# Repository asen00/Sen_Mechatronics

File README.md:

# MECH_ENG 433: Advanced Mechatronics
Northwestern University [MECH_ENG 433: Advanced Mechatronics](https://www.mccormick.northwestern.edu/mechanical/academics/courses/descriptions/433-advanced-mechatronics.html) taught by Nick Marchuk, Spring 2023

Details about assignments can be found [here](https://github.com/ndm736/ME433_2023/wiki).

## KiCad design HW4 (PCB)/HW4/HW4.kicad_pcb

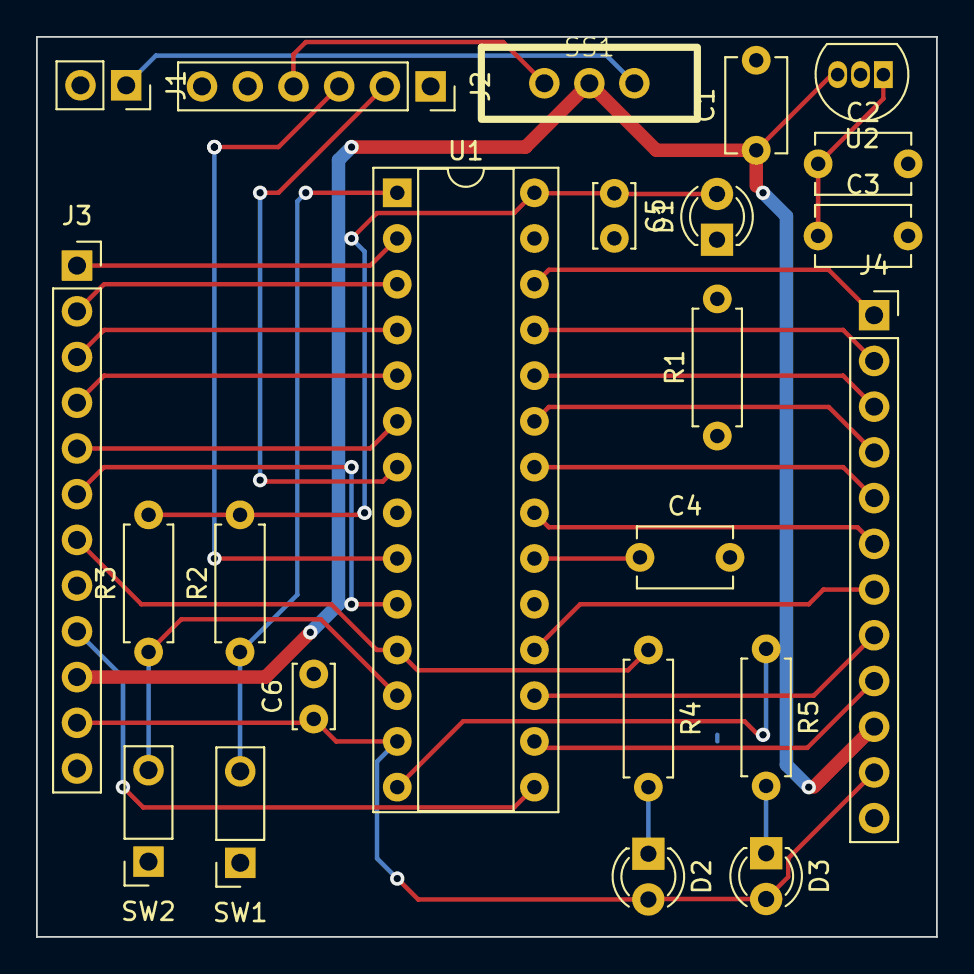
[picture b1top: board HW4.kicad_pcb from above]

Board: 2 copper layers, 50.0 x 50.0 mm, 23 parts (0 on the bottom side), 29 nets.

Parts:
C1, C2, C3, C4: 1 uF; C_Disc_D5.1mm_W3.2mm_P5.00mm
C5, C6: 0.1 uF; C_Disc_D3.4mm_W2.1mm_P2.50mm
D1: RED; LED_D3.0mm
D2: GREEN; LED_D3.0mm
D3: YELLOW; LED_D3.0mm
J1: BATTERY; PinSocket_1x02_P2.54mm_Vertical
J2: CP2102; PinSocket_1x06_P2.54mm_Vertical
J3: LEFT; PinSocket_1x12_P2.54mm_Vertical
J4: RIGHT; PinSocket_1x12_P2.54mm_Vertical
R1, R4, R5: 330; R_Axial_DIN0207_L6.3mm_D2.5mm_P7.62mm_Horizontal
R2, R3: 10k; R_Axial_DIN0207_L6.3mm_D2.5mm_P7.62mm_Horizontal
SS1: SLIDE; SlideSwitch
SW1: MCLR; PushButton
SW2: USER; PushButton
U1: PIC32; DIP-28_W7.62mm_Socket
U2: AP7381-33V; TO-92L_Inline

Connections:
+3.3V: C2.1, C3.1, C6.1, D2.2 (A), D3.2 (A), J3.11, J4.11, U1.13 (VDD), U2.1 (VO)
+5V: J2.4, SS1.1
/A0: J3.1, U1.2 (A0)
/A1: J3.2, U1.3 (A1)
/B0: J3.3, U1.4 (B0)
/B1: J3.4, U1.5 (B1)
/B2: J3.5, U1.6 (B2)
/B6: J3.9, U1.15 (B6)
/B7: J4.9, U1.16 (B7)
/B8: J4.8, U1.17 (B8)
/B9: J4.7, U1.18 (B9)
/B10: J4.6, U1.21 (B10)
/B11: J4.5, U1.22 (B11)
/B12: J4.4, U1.23 (B12)
/B13: J4.3, U1.24 (B13)
/B14: J4.2, U1.25 (B14)
/B15: J4.1, U1.26 (B15)
/GREEN: J3.7, R4.1, U1.11 (B4)
/MCLR: R2.1, SW1.2, U1.1 (~MCLR)
/U1RX: J2.3, U1.9 (A2)
/U1TX: J2.2, U1.7 (B3)
/USER: R3.1, SW2.2, U1.12 (A4)
/Vin: C1.1, C5.1, D1.2 (A), J3.6, J3.10, J4.10, R2.2, R3.2, R5.1, SS1.2, U1.10 (A3), U1.14 (B5), U1.28 (AVDD), U2.3 (VI)
GND: C1.2, C2.2, C3.2, C4.2, C5.2, C6.2, J1.2, J2.6, J3.12, J4.12, R1.1, SW1.1, SW2.1, U1.8 (VSS), U1.19 (VSS), U1.27 (AVSS), U2.2 (GND)
unnamed: D1.1 (K), R1.2
unnamed: D2.1 (K), R4.2
unnamed: D3.1 (K), R5.2
unnamed: J1.1, SS1.3
unnamed: C4.1, U1.20 (VCAP)

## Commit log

2023-04-28 All MPLABX projects
2023-04-30 HW3 Start
2023-04-30 HW3 Setup
2023-04-30 Stuck
    Need to check code with Nick; ask Nick how to run plotter.py and template.c simultaneously; ask Nick how to run terminal emulator.
2023-05-01 HW4 schematic complete
    Couldn't import slide switch library so made one myself; check with Nick if it works
2023-05-01 HW3 Finished
2023-05-02 HW5 Setup
2023-05-02 HW5 Stuck
2023-05-03 HW5 Complete
2023-05-03 HW6 Stuck
    Yellow LED not blinking...
2023-05-03 HW5 Stuck 2
    PIC LEDs functioning; unable to turn on GP7
2023-05-04 HW6 complete!
2023-05-04 HW6 project folder renamed
2023-05-04 HW7 complete
2023-05-04 HW9 setup
2023-05-04 Unfiltered plots done
2023-05-04 Done with all but FIR
2023-05-04 Need to fix bug in FIR func
2023-05-04 HW8 Setup
2023-05-04 HW9 complete
2023-05-04 HW8 in progress, works sometimes but very fickle
2023-05-05 HW8 string prints
2023-05-05 Strings printing, accelerometer working, just can't make them work together
2023-05-05 Printing az values as expected, need to figure out fps part
2023-05-07 HW8 complete
2023-05-07 HW10 setup
2023-05-08 Think I've written the functions but it won't work
2023-05-09 LEDs turning on, colors are off
2023-05-09 HW10 complete
2023-05-10 HW11 complete
    Copied from CIRCUITPY folder
2023-06-06 HW13
2023-06-06 HW15 done
